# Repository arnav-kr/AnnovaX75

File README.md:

# Annova X75

A 75% Mechanical Keyboard, custom built from scratch.

## Features
- 75% Exploded Layout
- Cherry MX Brown Switches
- RMK + Vial Firmware Support (Rust-based firmware with real-time Vial configuration)
- Hot-swappable Sockets
- Minimalist Sleek Design
- Customizable Knob
- Side mount USB-C Port
- 6° Typing Angle
- Sandwich Mount

## Build Guide

### PCB
The PCB is designed to be compatible with Cherry MX switches and features hot-swappable kalih sockets.
| Schematics |
| --- |
|  |

| PCB (All Layers)|
| --- |
|  |

| PCB (Front Layer)|
| --- |
|  |

| PCB (Back Layer)|
| --- |
|  |

| PCB Render (Front)|
| --- |
|  |

| PCB Render (Back)|
| --- |
|  |

### Case

The case is designed to be 3D printed and features a sandwich mount design with a 6° typing angle. The bottom case, top case, plate, and knob are all designed to be printed.

| Case Full|
| --- |
|  |

| Case Top|
| --- |
|  |

| Plate|
| --- |
|  |

| Case Bottom|
| --- |
|  |
|  |

| Knob|
| --- |
|  |

### BOM

| Item                               | Quantity | Cost (USD)* | Purchase Link                                                                                                                  |
| ---------------------------------- | -------- | ----------- | ------------------------------------------------------------------------------------------------------------------------------ |
| 1N4148 Diodes                      | 90 Pack  | 1.52        | https://stackskb.com/store/1n4148-through-hole-diode/                                                                          |
| Akko Bittersweet Switch            | 90 Pack  | 34          | https://stackskb.com/store/akko-bittersweet-switch-pack-of-45/                                       |
| EC11 Rotary Encoder                | 1        | 0.43        | https://www.flyrobo.in/ec11-rotary-encoder-half-shaft-handle-potentiometer-15mm                                                |
| Orpheus Pico                       | 1        | -           | Hack Club                                                                                                                      |
| Gateron Hotswap Sockets            | 90 Pack  | 11.16       | https://stackskb.com/store/gateron-hotswap-sockets/                                                                           |
| Durock v2 Stabilizers Set          | 1        | 17.98       | https://stackskb.com/store/durock-clear-screw-in-stabilizers-v2/?attribute_combination=4%2B1+Set&attribute_spacebar-size=6.25U |
| Keycap Set                         | 1        | 22.29       | https://curiositycaps.in/products/apollo-inspired-quality-cherry-doubleshot-pbt-keycaps?variant=51076299850009                                                                                                                          |
| Socket Head M3x12 Screws           | 3        | 0.3         | https://onlyscrews.in/products/hex-allen-socket-head-m3-x-12-screw-pack-of-20                                                  |
| Socket Head M3x25 Screws           | 3        | 0.3         | https://onlyscrews.in/products/m3-x-25mm-hex-allen-socket-head-ss-304-screw                                                    |
| M3 X 4mm Brass Threaded Inserts    | 6        | 0.3         | https://onlyscrews.in/products/m4-x-4mm-brass-threaded-inserts                                                                 |
| Bottom Case, Top Case, Plate, Knob | 1        | -           | (3D Printed)                                                                                                                   |
| Bottom Rubber Feet                 | 4        | 2.13        | https://www.amazon.in/Miramar-Adhesive-Non-Slip-Furniture-Hemispherical/dp/B0BLN4TCPT                                                                          |
| PCB                                | 1        | 58.2        | https://pcbpower.com                                                                                                            |

for detailed bom check out [BOM.csv](BOM.csv)

Cost is as of 28/12/2025

## Author
[Arnav Kumar](https://github.com/arnav-kr)

## License
This project is licensed under the [AGPL-3.0 License](LICENSE).

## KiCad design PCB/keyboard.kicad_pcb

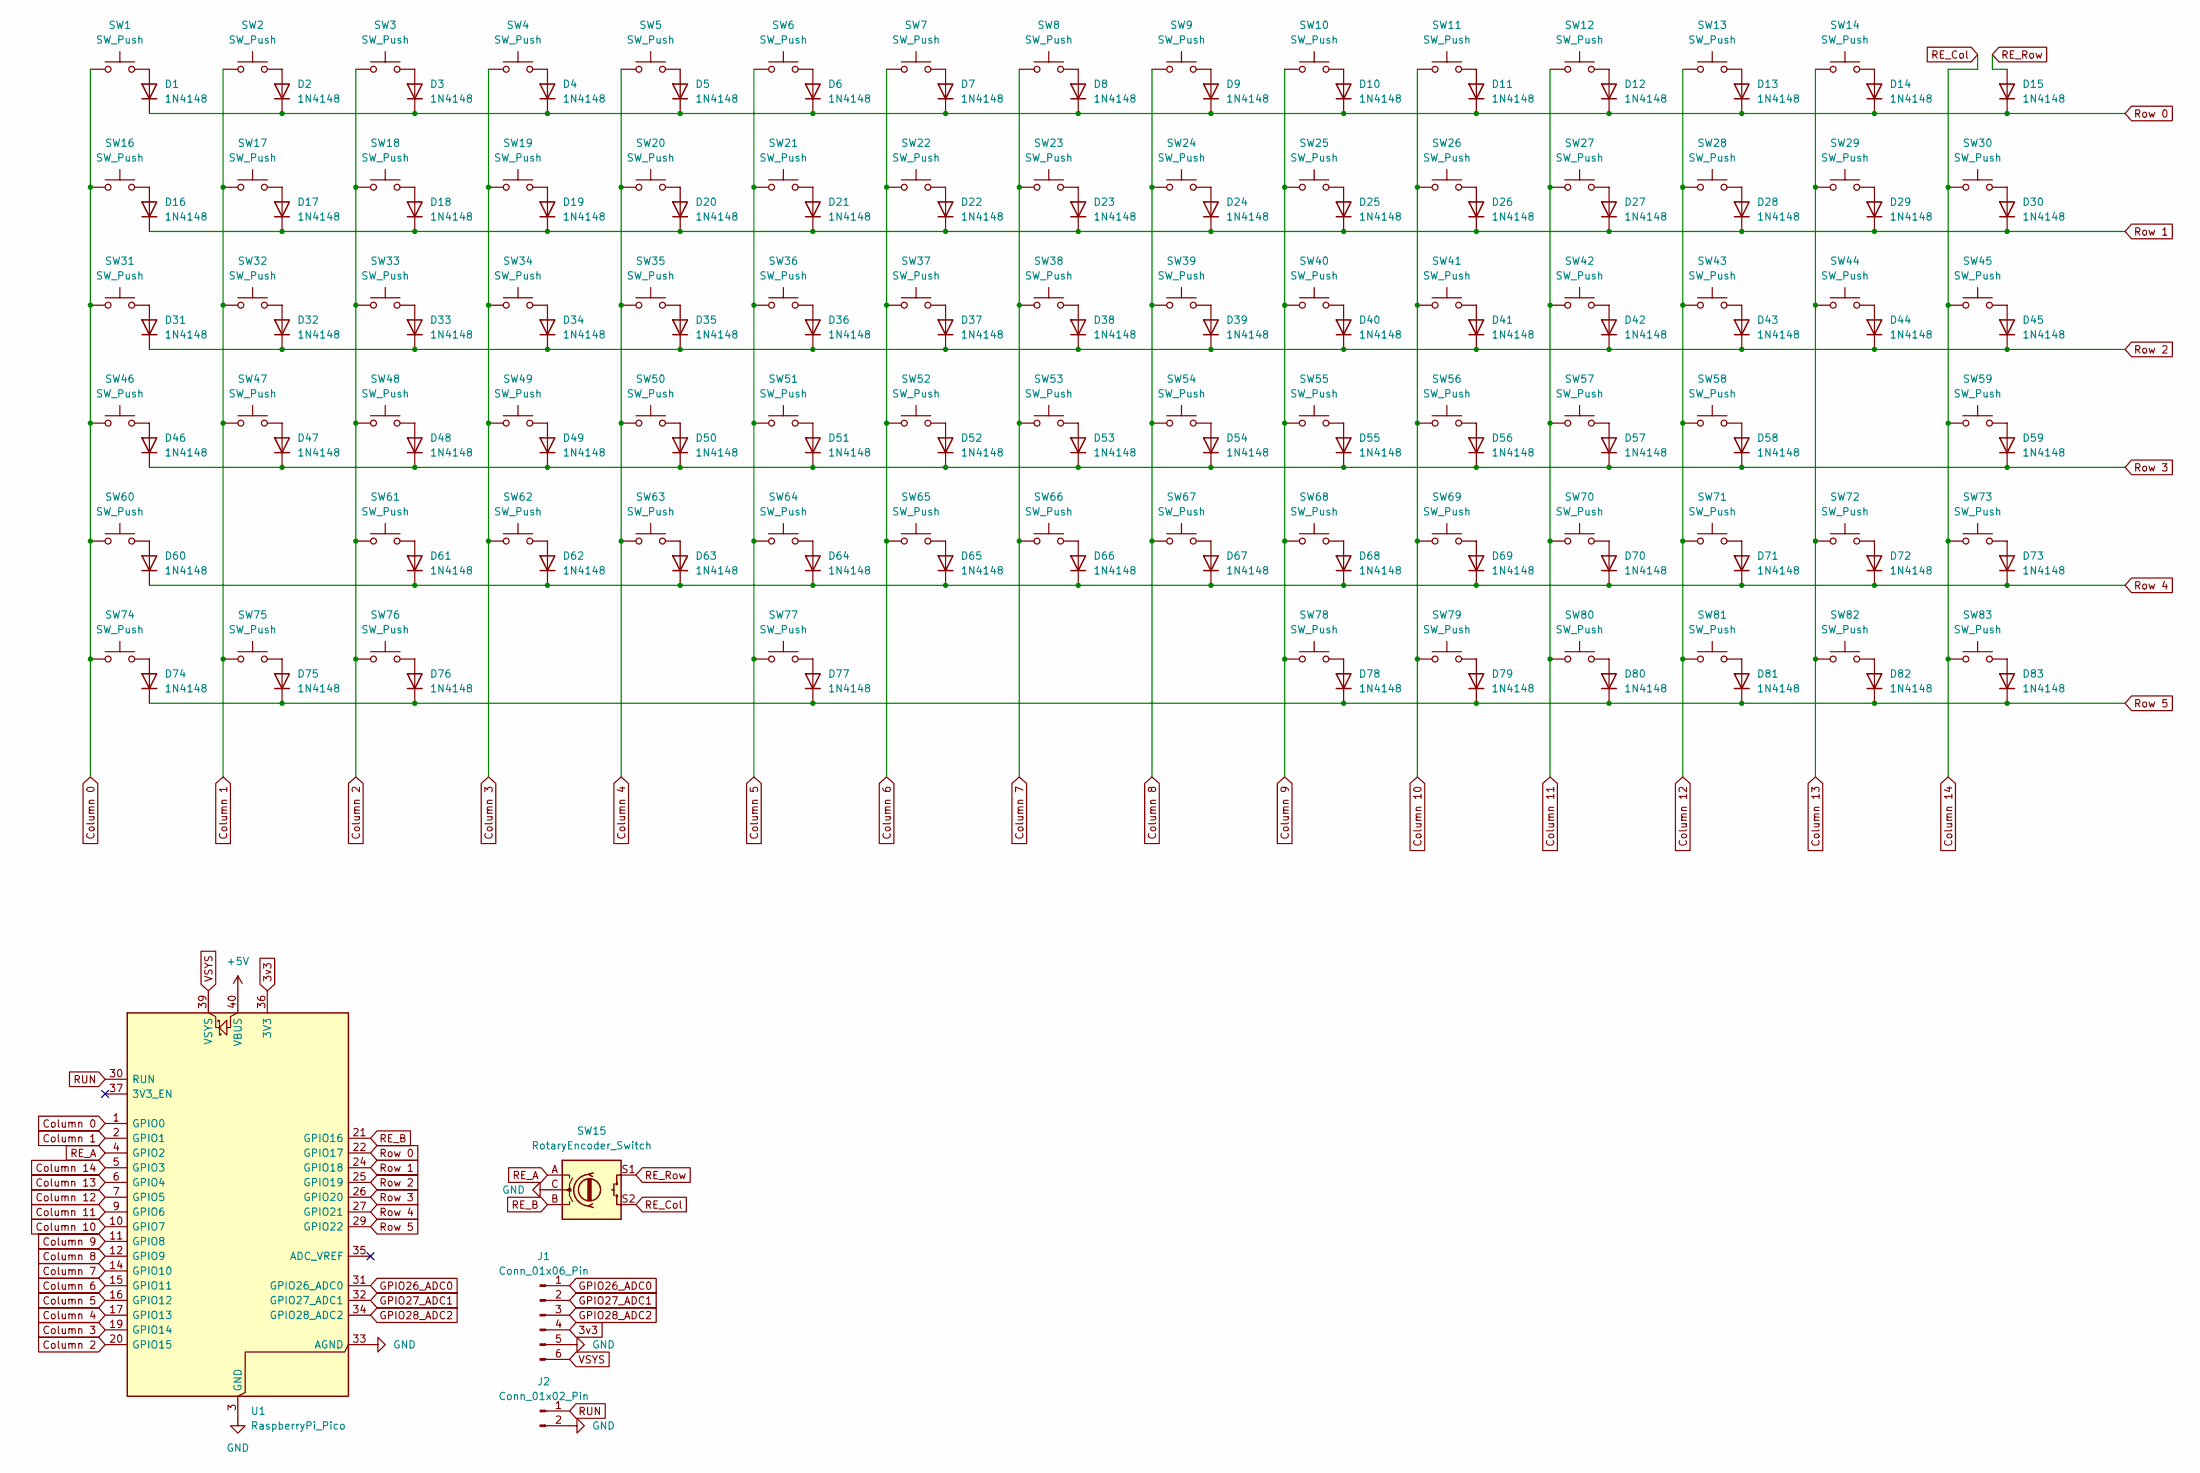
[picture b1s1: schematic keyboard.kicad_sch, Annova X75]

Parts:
D1, D2, D3, D4, D5, D6, D7, D8, D9, D10, D11, D12, D13, D14, D15, D16, D17, D18, D19, D20, D21, D22, D23, D24, D25, D26, D27, D28, D29, D30, D31, D32, D33, D34, D35, D36, D37, D38, D39, D40, D41, D42, D43, D44, D45, D46, D47, D48, D49, D50, D51, D52, D53, D54, D55, D56, D57, D58, D59, D60, D61, D62, D63, D64, D65, D66, D67, D68, D69, D70, D71, D72, D73, D74, D75, D76, D77, D78, D79, D80, D81, D82, D83: 1N4148; D_DO-35_SOD27_P7.62mm_Horizontal
J1: Conn_01x06_Pin; PinHeader_1x06_P2.54mm_Vertical
J2: Conn_01x02_Pin; PinHeader_1x02_P2.54mm_Vertical
SW1, SW2, SW3, SW4, SW5, SW6, SW7, SW8, SW9, SW10, SW11, SW12, SW13, SW14, SW16, SW17, SW18, SW19, SW20, SW21, SW22, SW23, SW24, SW25, SW26, SW27, SW28, SW30, SW32, SW33, SW34, SW35, SW36, SW37, SW38, SW39, SW40, SW41, SW42, SW43, SW45, SW47, SW48, SW49, SW50, SW51, SW52, SW53, SW54, SW55, SW56, SW57, SW59, SW61, SW62, SW63, SW64, SW65, SW66, SW67, SW68, SW69, SW70, SW72, SW73, SW78, SW79, SW80, SW81, SW82, SW83: SW_Push; SW_Hotswap_Kailh_MX_Plated_1.00u_With_Switch
SW15: RotaryEncoder_Switch; Encoder_EC11_MX_Combo
SW29: SW_Push; SW_Hotswap_Kailh_MX_Plated_2.00u_With_Switch
SW31, SW44: SW_Push; SW_Hotswap_Kailh_MX_Plated_1.50u_With_Switch
SW46, SW71: SW_Push; SW_Hotswap_Kailh_MX_Plated_1.75u_With_Switch
SW58, SW60: SW_Push; SW_Hotswap_Kailh_MX_Plated_2.25u_With_Switch
SW74, SW75, SW76: SW_Push; SW_Hotswap_Kailh_MX_Plated_1.25u_With_Switch
SW77: SW_Push; SW_Hotswap_Kailh_MX_Plated_6.25u_With_Switch
U1: RaspberryPi_Pico; RaspberryPi_Pico_THT

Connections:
3v3: J1.4, U1.36 (3V3)
+5V: U1.40 (VBUS)
Column 0: SW1.1, SW16.1, SW31.1, SW46.1, SW60.1, SW74.1, U1.1 (GPIO0)
Column 1: SW2.1, SW17.1, SW32.1, SW47.1, SW75.1, U1.2 (GPIO1)
Column 2: SW3.1, SW18.1, SW33.1, SW48.1, SW61.1, SW76.1, U1.20 (GPIO15)
Column 3: SW4.1, SW19.1, SW34.1, SW49.1, SW62.1, U1.19 (GPIO14)
Column 4: SW5.1, SW20.1, SW35.1, SW50.1, SW63.1, U1.17 (GPIO13)
Column 5: SW6.1, SW21.1, SW36.1, SW51.1, SW64.1, SW77.1, U1.16 (GPIO12)
Column 6: SW7.1, SW22.1, SW37.1, SW52.1, SW65.1, U1.15 (GPIO11)
Column 7: SW8.1, SW23.1, SW38.1, SW53.1, SW66.1, U1.14 (GPIO10)
Column 8: SW9.1, SW24.1, SW39.1, SW54.1, SW67.1, U1.12 (GPIO9)
Column 9: SW10.1, SW25.1, SW40.1, SW55.1, SW68.1, SW78.1, U1.11 (GPIO8)
Column 10: SW11.1, SW26.1, SW41.1, SW56.1, SW69.1, SW79.1, U1.10 (GPIO7)
Column 11: SW12.1, SW27.1, SW42.1, SW57.1, SW70.1, SW80.1, U1.9 (GPIO6)
Column 12: SW13.1, SW28.1, SW43.1, SW58.1, SW71.1, SW81.1, U1.7 (GPIO5)
Column 13: SW14.1, SW29.1, SW44.1, SW72.1, SW82.1, U1.6 (GPIO4)
Column 14: SW15.S2, SW30.1, SW45.1, SW59.1, SW73.1, SW83.1, U1.5 (GPIO3)
GND: J1.5, J2.2, SW15.C, U1.3 (GND), U1.8 (GND), U1.13 (GND), U1.18 (GND), U1.23 (GND), U1.28 (GND), U1.33 (AGND), U1.38 (GND)
GPIO26_ADC0: J1.1, U1.31 (GPIO26_ADC0)
GPIO27_ADC1: J1.2, U1.32 (GPIO27_ADC1)
GPIO28_ADC2: J1.3, U1.34 (GPIO28_ADC2)
unnamed: D1.2 (A), SW1.2
unnamed: D2.2 (A), SW2.2
unnamed: D3.2 (A), SW3.2
unnamed: D4.2 (A), SW4.2
unnamed: D5.2 (A), SW5.2
unnamed: D6.2 (A), SW6.2
unnamed: D7.2 (A), SW7.2
unnamed: D8.2 (A), SW8.2
unnamed: D9.2 (A), SW9.2
unnamed: D10.2 (A), SW10.2
unnamed: D11.2 (A), SW11.2
unnamed: D12.2 (A), SW12.2
unnamed: D13.2 (A), SW13.2
unnamed: D14.2 (A), SW14.2
unnamed: D16.2 (A), SW16.2
unnamed: D17.2 (A), SW17.2
unnamed: D18.2 (A), SW18.2
unnamed: D19.2 (A), SW19.2
unnamed: D20.2 (A), SW20.2
unnamed: D21.2 (A), SW21.2
unnamed: D22.2 (A), SW22.2
unnamed: D23.2 (A), SW23.2
unnamed: D24.2 (A), SW24.2
unnamed: D25.2 (A), SW25.2
unnamed: D26.2 (A), SW26.2
unnamed: D27.2 (A), SW27.2
unnamed: D28.2 (A), SW28.2
unnamed: D29.2 (A), SW29.2
unnamed: D30.2 (A), SW30.2
unnamed: D31.2 (A), SW31.2
unnamed: D32.2 (A), SW32.2
unnamed: D33.2 (A), SW33.2
unnamed: D34.2 (A), SW34.2
unnamed: D35.2 (A), SW35.2
unnamed: D36.2 (A), SW36.2
unnamed: D37.2 (A), SW37.2
unnamed: D38.2 (A), SW38.2
unnamed: D39.2 (A), SW39.2
unnamed: D40.2 (A), SW40.2
unnamed: D41.2 (A), SW41.2
unnamed: D42.2 (A), SW42.2
unnamed: D43.2 (A), SW43.2
unnamed: D44.2 (A), SW44.2
unnamed: D45.2 (A), SW45.2
unnamed: D46.2 (A), SW46.2
unnamed: D47.2 (A), SW47.2
unnamed: D48.2 (A), SW48.2
unnamed: D49.2 (A), SW49.2
unnamed: D50.2 (A), SW50.2
unnamed: D51.2 (A), SW51.2
unnamed: D52.2 (A), SW52.2
unnamed: D53.2 (A), SW53.2
unnamed: D54.2 (A), SW54.2
unnamed: D55.2 (A), SW55.2
unnamed: D56.2 (A), SW56.2
unnamed: D57.2 (A), SW57.2
unnamed: D58.2 (A), SW58.2
unnamed: D59.2 (A), SW59.2
unnamed: D60.2 (A), SW60.2
unnamed: D61.2 (A), SW61.2
unnamed: D62.2 (A), SW62.2
unnamed: D63.2 (A), SW63.2
unnamed: D64.2 (A), SW64.2
unnamed: D65.2 (A), SW65.2
unnamed: D66.2 (A), SW66.2
unnamed: D67.2 (A), SW67.2
unnamed: D68.2 (A), SW68.2
unnamed: D69.2 (A), SW69.2
unnamed: D70.2 (A), SW70.2
unnamed: D71.2 (A), SW71.2
unnamed: D72.2 (A), SW72.2
unnamed: D73.2 (A), SW73.2
unnamed: D74.2 (A), SW74.2
unnamed: D75.2 (A), SW75.2
unnamed: D76.2 (A), SW76.2
unnamed: D77.2 (A), SW77.2
unnamed: D78.2 (A), SW78.2
unnamed: D79.2 (A), SW79.2
unnamed: D80.2 (A), SW80.2
unnamed: D81.2 (A), SW81.2
unnamed: D82.2 (A), SW82.2
unnamed: D83.2 (A), SW83.2
RE_A: SW15.A, U1.4 (GPIO2)
RE_B: SW15.B, U1.21 (GPIO16)
RE_Row: D15.2 (A), SW15.S1
RUN: J2.1, U1.30 (RUN)
Row 0: D1.1 (K), D2.1 (K), D3.1 (K), D4.1 (K), D5.1 (K), D6.1 (K), D7.1 (K), D8.1 (K), D9.1 (K), D10.1 (K), D11.1 (K), D12.1 (K), D13.1 (K), D14.1 (K), D15.1 (K), U1.22 (GPIO17)
Row 1: D16.1 (K), D17.1 (K), D18.1 (K), D19.1 (K), D20.1 (K), D21.1 (K), D22.1 (K), D23.1 (K), D24.1 (K), D25.1 (K), D26.1 (K), D27.1 (K), D28.1 (K), D29.1 (K), D30.1 (K), U1.24 (GPIO18)
Row 2: D31.1 (K), D32.1 (K), D33.1 (K), D34.1 (K), D35.1 (K), D36.1 (K), D37.1 (K), D38.1 (K), D39.1 (K), D40.1 (K), D41.1 (K), D42.1 (K), D43.1 (K), D44.1 (K), D45.1 (K), U1.25 (GPIO19)
Row 3: D46.1 (K), D47.1 (K), D48.1 (K), D49.1 (K), D50.1 (K), D51.1 (K), D52.1 (K), D53.1 (K), D54.1 (K), D55.1 (K), D56.1 (K), D57.1 (K), D58.1 (K), D59.1 (K), U1.26 (GPIO20)
Row 4: D60.1 (K), D61.1 (K), D62.1 (K), D63.1 (K), D64.1 (K), D65.1 (K), D66.1 (K), D67.1 (K), D68.1 (K), D69.1 (K), D70.1 (K), D71.1 (K), D72.1 (K), D73.1 (K), U1.27 (GPIO21)
Row 5: D74.1 (K), D75.1 (K), D76.1 (K), D77.1 (K), D78.1 (K), D79.1 (K), D80.1 (K), D81.1 (K), D82.1 (K), D83.1 (K), U1.29 (GPIO22)
VSYS: J1.6, U1.39 (VSYS)

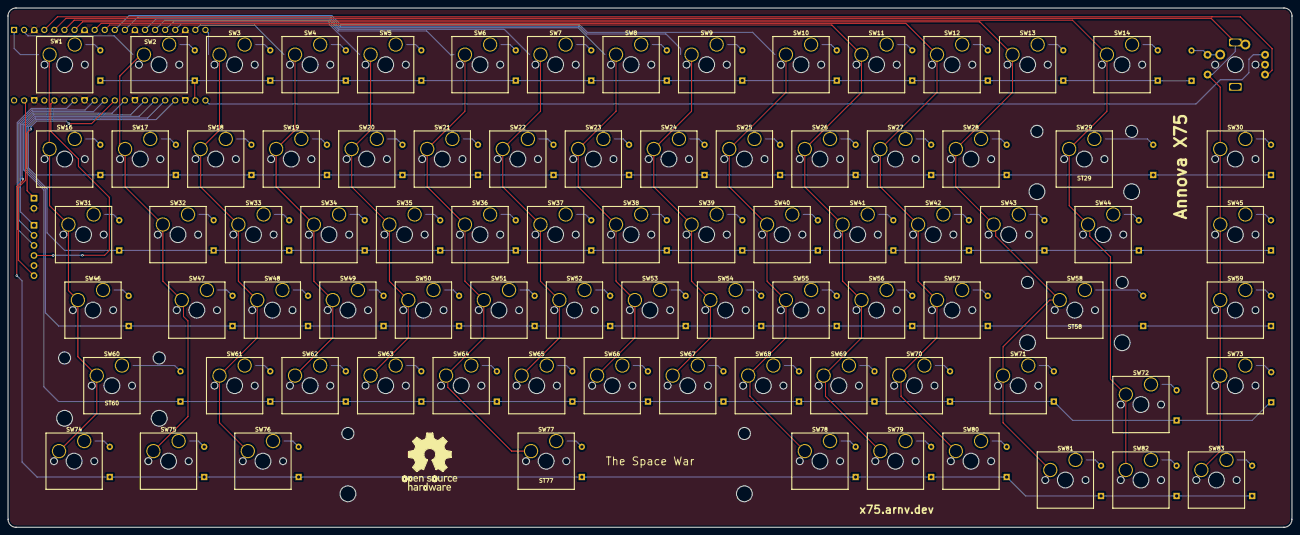
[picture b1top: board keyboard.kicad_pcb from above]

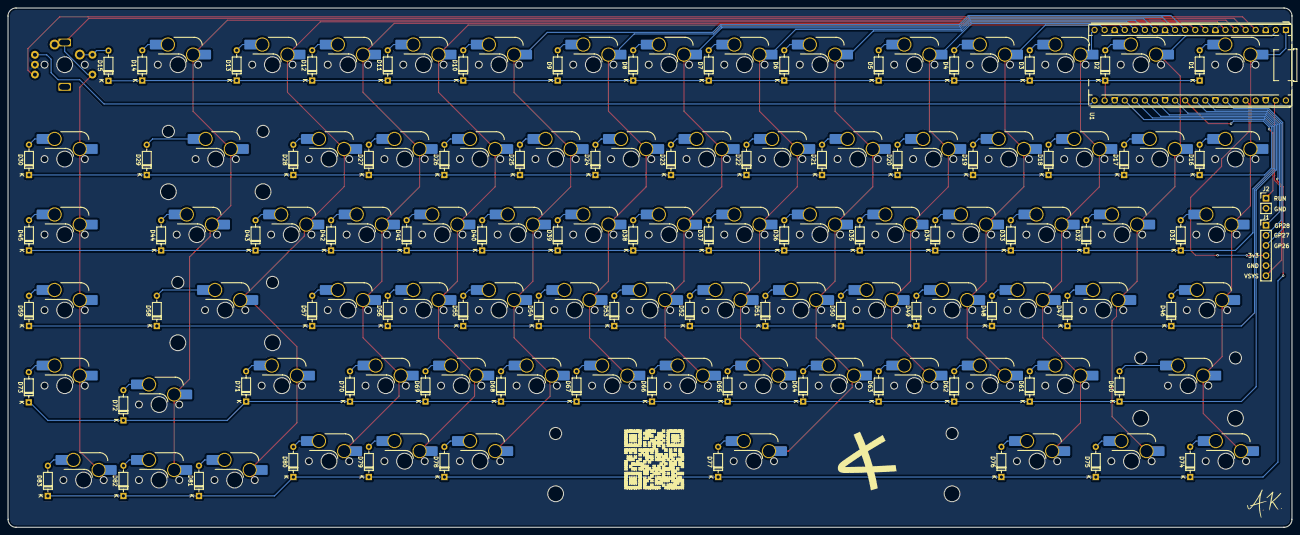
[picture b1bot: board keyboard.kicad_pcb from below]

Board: 2 copper layers, 323.9 x 131.0 mm, 173 parts (86 on the bottom side), 113 nets.

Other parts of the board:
ST29, ST58, ST60: Stabilizer_Cherry_MX_2.00u
ST77: Stabilizer_Cherry_MX_6.25u

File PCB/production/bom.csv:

Designator,Footprint,Quantity,Value,LCSC Part #
"D1, D10, D11, D12, D13, D14, D15, D16, D17, D18, D19, D2, D20, D21, D22, D23, D24, D25, D26, D27, D28, D29, D3, D30, D31, D32, D33, D34, D35, D36, D37, D38, D39, D4, D40, D41, D42, D43, D44, D45, D46, D47, D48, D49, D5, D50, D51, D52, D53, D54, D55, D56, D57, D58, D59, D6, D60, D61, D62, D63, D64, D65, D66, D67, D68, D69, D7, D70, D71, D72, D73, D74, D75, D76, D77, D78, D79, D8, D80, D81, D82, D83, D9",D_DO-35_SOD27_P7.62mm_Horizontal,83,1N4148,
J1,PinHeader_1x06_P2.54mm_Vertical,1,Conn_01x06_Pin,
J2,PinHeader_1x02_P2.54mm_Vertical,1,Conn_01x02_Pin,
"SW1, SW10, SW11, SW12, SW13, SW14, SW16, SW17, SW18, SW19, SW2, SW20, SW21, SW22, SW23, SW24, SW25, SW26, SW27, SW28, SW3, SW30, SW32, SW33, SW34, SW35, SW36, SW37, SW38, SW39, SW4, SW40, SW41, SW42, SW43, SW45, SW47, SW48, SW49, SW5, SW50, SW51, SW52, SW53, SW54, SW55, SW56, SW57, SW59, SW6, SW61, SW62, SW63, SW64, SW65, SW66, SW67, SW68, SW69, SW7, SW70, SW72, SW73, SW78, SW79, SW8, SW80, SW81, SW82, SW83, SW9",SW_Hotswap_Kailh_MX_Plated_1.00u_With_Switch,71,SW_Push,
SW15,Encoder_EC11_MX_Combo,1,RotaryEncoder_Switch,
SW29,SW_Hotswap_Kailh_MX_Plated_2.00u_With_Switch,1,SW_Push,
"SW31, SW44",SW_Hotswap_Kailh_MX_Plated_1.50u_With_Switch,2,SW_Push,
"SW46, SW71",SW_Hotswap_Kailh_MX_Plated_1.75u_With_Switch,2,SW_Push,
"SW58, SW60",SW_Hotswap_Kailh_MX_Plated_2.25u_With_Switch,2,SW_Push,
"SW74, SW75, SW76",SW_Hotswap_Kailh_MX_Plated_1.25u_With_Switch,3,SW_Push,
SW77,SW_Hotswap_Kailh_MX_Plated_6.25u_With_Switch,1,SW_Push,
U1,RaspberryPi_Pico_THT,1,RaspberryPi_Pico,

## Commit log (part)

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2025-06-09 init: project
2025-06-09 docs: add LICENSE
2025-06-09 FUNDING.yml
2025-06-22 feat: website
2025-06-22 Create CNAME
2025-06-22 feat: added seo tags
2025-06-22 docs: update readme
2025-06-22 chore: optimize assets
2025-06-22 try+fix: blurs
2025-06-22 try+fix: blur on android
2025-06-22 fix: blur on chromium browsers
2025-06-22 refactor
2025-06-24 feat: QMK + VIA firmware
2025-07-16 update: description
2025-07-19 docs: update bom and highlights
2025-10-28 feat: update CAD models
2025-10-28 feat: update renders
2025-10-28 feat: update pcb render
2025-10-30 feat: update pcb renders
2025-10-30 feat: update keyboard pcb and production files
2025-10-30 [ImgBot] Optimize images
    *Total -- 3,299.70kb -> 2,739.83kb (16.97%)
    /assets/pcb_back_render.png -- 399.94kb -> 294.41kb (26.39%)
    /assets/pcb_front_render.png -- 381.52kb -> 287.45kb (24.66%)
    /assets/pcb_front.png -- 287.47kb -> 216.78kb (24.59%)
    /assets/schematics.png -- 298.86kb -> 225.50kb (24.55%)
    /assets/pcb_back.png -- 306.46kb -> 233.61kb (23.77%)
2025-10-30 docs: update bom
2025-10-30 docs: bom file
2025-10-30 docs: update bom with shipping
2025-10-30 docs: update readme bom
2025-11-19 feat: production files, bom changes
2025-12-10 chore: model update
2025-12-30 update gerbers
2026-01-04 docs: update BOM.csv
